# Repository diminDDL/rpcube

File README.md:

# rpcube

Welcome to `rpcube`, the ultimate compact solution for integrating the RP2040 into your designs seamlessly. This project presents an all-in-one small BGA package that brings the powerful RP2040 to your fingertips. 

## Features

- **Compact Size**: With a tiny footprint of just 16.5x16.5mm, `rpcube` is designed to fit into the smallest of spaces while providing the full capabilities of the RP2040.

- **Integrated Components**: The package includes EEPROM, all necessary bypass capacitors, and an LDO to allow for direct 5V input, stepping it down internally.
- **Full GPIO Access**: All GPIOs as well as the SWD lines of the RP2040 are exposed and accessible, ensuring you can leverage the full power of the microcontroller for your projects.
- **Versatile Assembly Options**: Whether you prefer to use solder paste and stencils or go for manual soldering with an iron, `rpcube` accommodates various assembly methods to suit your workflow:
  - **Top Side Assembly**: Begin by assembling the top side using solder paste and hot air or a reflow oven.
  - **Bottom Balls Creation**: Create the bottom balls using a soldering iron with flux and a substantial amount of solder, or stack several stencils to dispense ample solder paste, then blast it with hot air for balls to form.
  - **Target PCB Solder Paste Method**: You can use the same stencil as for the bottom side on the target board, or if you already have the balls done, use just a bit of flux and reflow, the balls will attach themselves.
  - **Target PCB Via in Pad Integration**: You can also use untented vias in your target PCB. Incorporate untented vias in the places of the balls and solder them one by one with an iron.
  - **Wire Attachment for Prototyping**: Alternatively, attach wires directly to `rpcube` for quick and easy point-to-point prototyping.

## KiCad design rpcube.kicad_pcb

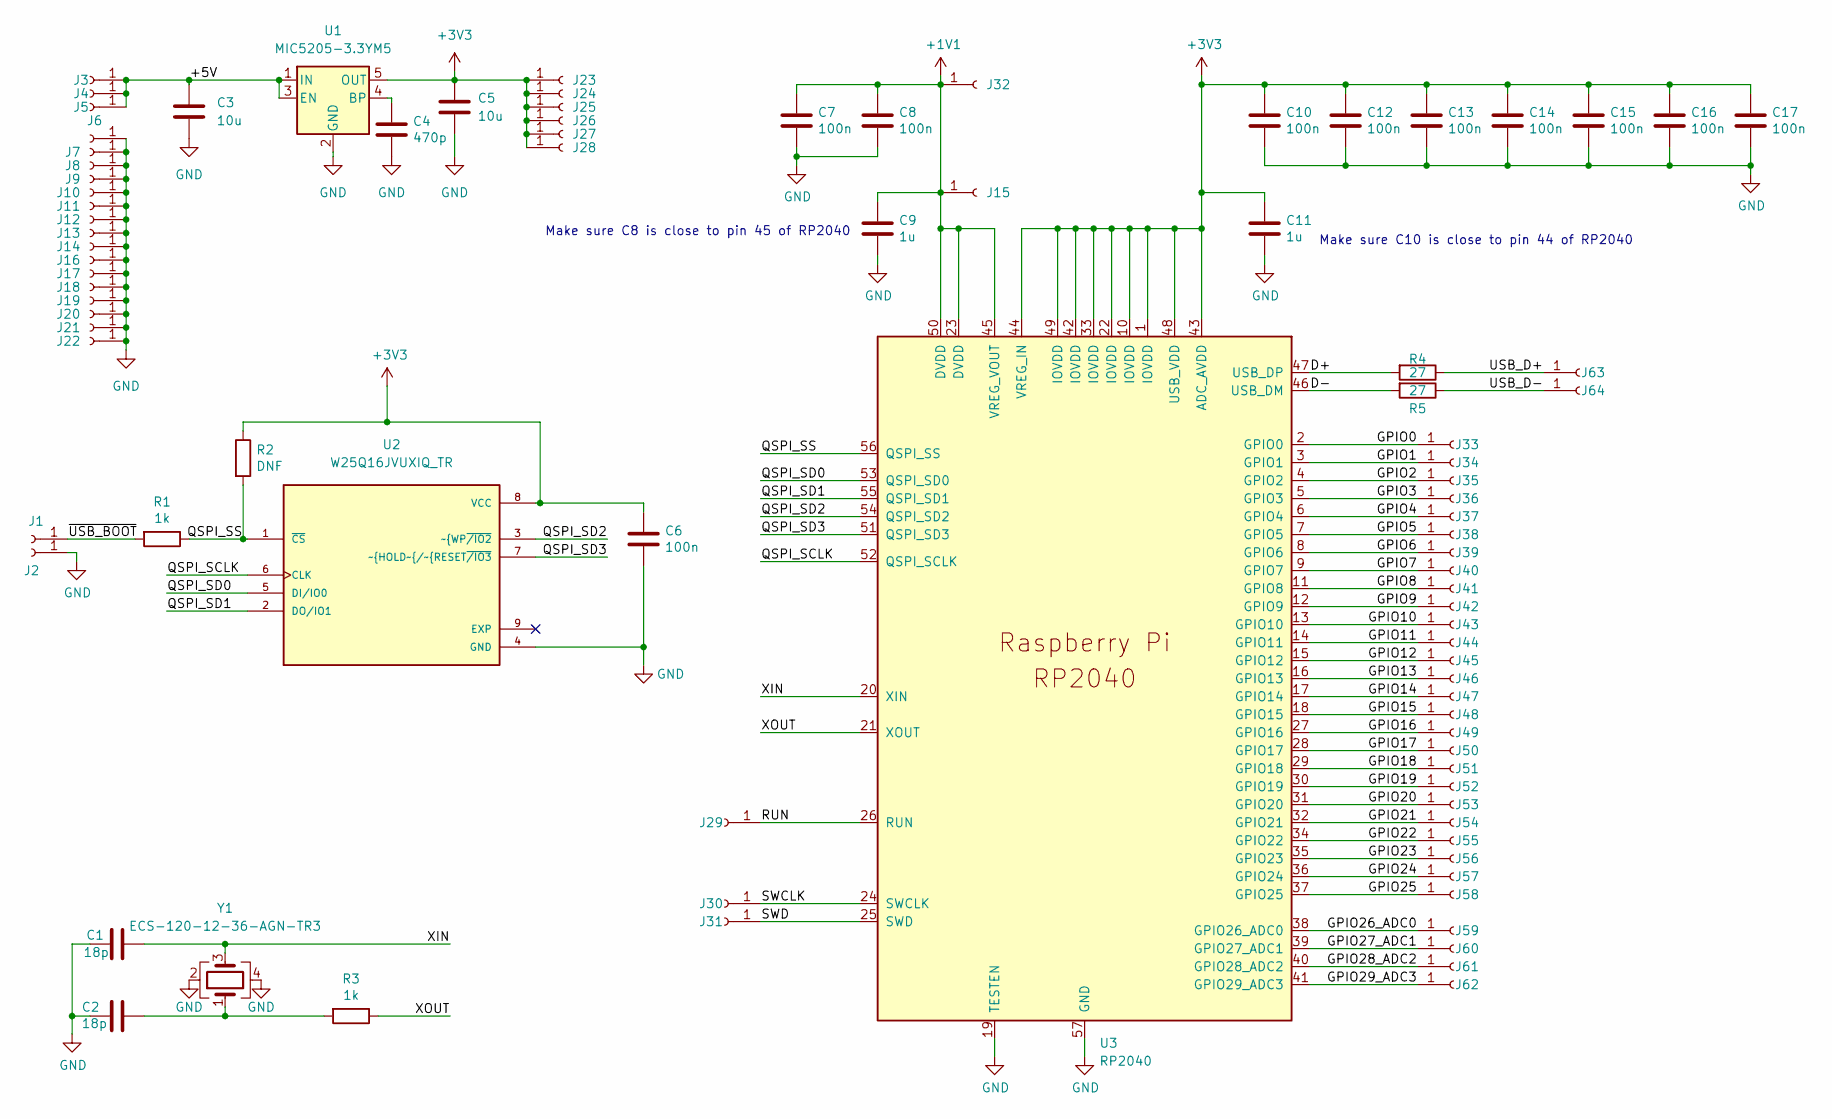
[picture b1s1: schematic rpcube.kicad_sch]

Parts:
C1, C2: 18p; C_0402_1005Metric
C3: 10u; C_0603_1608Metric
C4: 470p; C_0402_1005Metric
C5: 10u; C_0402_1005Metric
C6, C7, C8, C10, C12, C13, C14, C15, C16, C17: 100n; C_0402_1005Metric
C9, C11: 1u; C_0402_1005Metric
J1, J2, J3, J4, J5, J6, J7, J8, J9, J10, J11, J12, J13, J14, J15, J16, J17, J18, J19, J20, J21, J22, J23, J24, J25, J26, J27, J28, J29, J30, J31, J32, J33, J34, J35, J36, J37, J38, J39, J40, J41, J42, J43, J44, J45, J46, J47, J48, J49, J50, J51, J52, J53, J54, J55, J56, J57, J58, J59, J60, J61, J62, J63, J64: Conn_01x01_Female; BGA_PAD
R1, R3: 1k; R_0402_1005Metric
R2: DNF; R_0402_1005Metric
R4, R5: 27; R_0402_1005Metric
U1: MIC5205-3.3YM5; SOT-23-5
U2: W25Q16JVUXIQ_TR; IC_W25Q16JVUXIQ_TR; PARTREV H
U3: RP2040; RP2040-QFN-56
Y1: ECS-120-12-36-AGN-TR3; Crystal_SMD_2520-4Pin_2.5x2.0mm

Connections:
+1V1: C7.1, C8.1, C9.1, J15.1, J32.1, U3.23 (DVDD), U3.45 (VREG_VOUT), U3.50 (DVDD)
+3V3: C5.1, C6.1, C10.1, C11.1, C12.1, C13.1, C14.1, C15.1, C16.1, C17.1, J23.1, J24.1, J25.1, J26.1, J27.1, J28.1, R2.1, U1.5 (OUT), U2.8 (VCC), U3.1 (IOVDD), U3.10 (IOVDD), U3.22 (IOVDD), U3.33 (IOVDD), U3.42 (IOVDD), U3.43 (ADC_AVDD), U3.44 (VREG_IN), U3.48 (USB_VDD), U3.49 (IOVDD)
/+5V: C3.1, J3.1, J4.1, J5.1, U1.1 (IN), U1.3 (EN)
/D+: R4.2, U3.47 (USB_DP)
/D-: R5.2, U3.46 (USB_DM)
/GPIO0: J33.1, U3.2 (GPIO0)
/GPIO1: J34.1, U3.3 (GPIO1)
/GPIO2: J35.1, U3.4 (GPIO2)
/GPIO3: J36.1, U3.5 (GPIO3)
/GPIO4: J37.1, U3.6 (GPIO4)
/GPIO5: J38.1, U3.7 (GPIO5)
/GPIO6: J39.1, U3.8 (GPIO6)
/GPIO7: J40.1, U3.9 (GPIO7)
/GPIO8: J41.1, U3.11 (GPIO8)
/GPIO9: J42.1, U3.12 (GPIO9)
/GPIO10: J43.1, U3.13 (GPIO10)
/GPIO11: J44.1, U3.14 (GPIO11)
/GPIO12: J45.1, U3.15 (GPIO12)
/GPIO13: J46.1, U3.16 (GPIO13)
/GPIO14: J47.1, U3.17 (GPIO14)
/GPIO15: J48.1, U3.18 (GPIO15)
/GPIO16: J49.1, U3.27 (GPIO16)
/GPIO17: J50.1, U3.28 (GPIO17)
/GPIO18: J51.1, U3.29 (GPIO18)
/GPIO19: J52.1, U3.30 (GPIO19)
/GPIO20: J53.1, U3.31 (GPIO20)
/GPIO21: J54.1, U3.32 (GPIO21)
/GPIO22: J55.1, U3.34 (GPIO22)
/GPIO23: J56.1, U3.35 (GPIO23)
/GPIO24: J57.1, U3.36 (GPIO24)
/GPIO25: J58.1, U3.37 (GPIO25)
/GPIO26_ADC0: J59.1, U3.38 (GPIO26_ADC0)
/GPIO27_ADC1: J60.1, U3.39 (GPIO27_ADC1)
/GPIO28_ADC2: J61.1, U3.40 (GPIO28_ADC2)
/GPIO29_ADC3: J62.1, U3.41 (GPIO29_ADC3)
/QSPI_SCLK: U2.6 (CLK), U3.52 (QSPI_SCLK)
/QSPI_SD0: U2.5 (DI/IO0), U3.53 (QSPI_SD0)
/QSPI_SD1: U2.2 (DO/IO1), U3.55 (QSPI_SD1)
/QSPI_SD2: U2.3 (~WP~{/IO2), U3.54 (QSPI_SD2)
/QSPI_SD3: U2.7 (~HOLD~{/~{RESET~{/IO3), U3.51 (QSPI_SD3)
/QSPI_SS: R1.1, R2.2, U2.1 (~CS), U3.56 (QSPI_SS)
/RUN: J29.1, U3.26 (RUN)
/SWCLK: J30.1, U3.24 (SWCLK)
/SWD: J31.1, U3.25 (SWD)
/USB_D+: J63.1, R4.1
/USB_D-: J64.1, R5.1
/XIN: C1.1, U3.20 (XIN), Y1.3
/XOUT: R3.1, U3.21 (XOUT)
/~USB_BOOT: J1.1, R1.2
GND: C1.2, C2.2, C3.2, C4.2, C5.2, C6.2, C7.2, C8.2, C9.2, C10.2, C11.2, C12.2, C13.2, C14.2, C15.2, C16.2, C17.2, J2.1, J6.1, J7.1, J8.1, J9.1, J10.1, J11.1, J12.1, J13.1, J14.1, J16.1, J17.1, J18.1, J19.1, J20.1, J21.1, J22.1, U1.2 (GND), U2.4 (GND), U3.19 (TESTEN), U3.57 (GND), Y1.2, Y1.4
unnamed: C2.1, R3.2, Y1.1
unnamed: C4.1, U1.4 (BP)

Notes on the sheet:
Make sure C10 is close to pin 44 of RP2040
Make sure C8 is close to pin 45 of RP2040

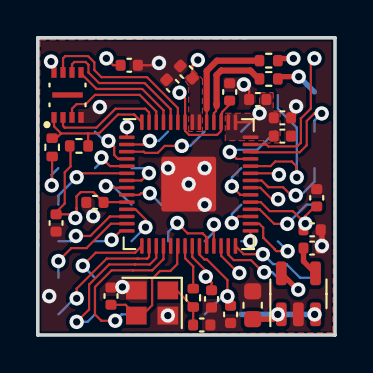
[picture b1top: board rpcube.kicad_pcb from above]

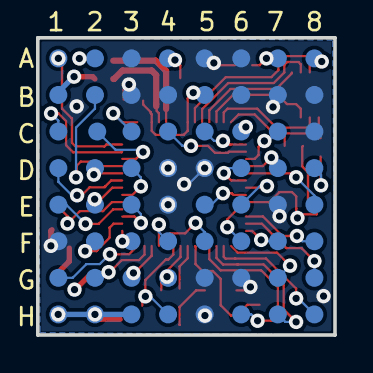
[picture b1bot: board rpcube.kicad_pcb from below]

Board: 4 copper layers, 16.5 x 16.5 mm, 90 parts (64 on the bottom side), 52 nets.

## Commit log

2023-01-29 finished PCB
2023-01-29 minor changes
2023-04-16 updated schematic
2023-06-04 added more images
2023-10-28 added renders
